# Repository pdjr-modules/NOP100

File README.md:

# NOP100

The **NOP100** project implements an
[NMEA 2000](https://en.wikipedia.org/wiki/NMEA_2000)
interface module with twin
[MikroBUS](https://www.mikroe.com/mikrobus)
sockets which allow specialisation of function by the addition of
[Click](https://www.mikroe.com/click) expansion cards.

[**NOP100** hardware](./hardware/README.md)
is based on the Teensy 4.0 micro-controller supported by a CAN
transceiver, parasitic power supply and a user configuration
interface.

[**NOP100** firmware](./firmware/README.md)
manages NMEA 2000 connectivity, user interaction and module
configuration and is easily extended by the addition of firmware
dedicated to operation of the installed MikroBus cards and the
integration of their function with NMEA 2000.

## Project organisation

```
NOP100/
  + firmware/            # NOP100 firmware...
    + modules/           # Folders for module specialisations
      + NOP100-SIM/        # Specialisation defining an NMEA switch input module
        + defines.h
        + definitions.h
        + includes.h
        + loop.h
        + setup.h
      + another module specialisation/
      + .../
    + NOP100.cpp         # NOP100 main application 
    + README.md
    + defines.h          # Symbolic link to a module specialisation
    + definitions.h      #   "       "
    + includes.h         #   "       "
    + loop.h             #   "       "
    + setup.h            #   "       "
  + hardware/            # NOP100 hardware...
    + gerber/            # Gerber files for PCB fabrication
    + kicad/             # Kicad design for the NOP100 motherboard
    + README.md
```

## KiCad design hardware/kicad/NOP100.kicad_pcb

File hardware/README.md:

# NOP100 hardware

This project thread provides a circuit design and PCB layout for an
NMEA 2000 interface module which uses
[MikroBus](https://www.mikroe.com/mikrobus)
[Click](https://mikroe.com/click) cards as its real-world interfaces.

The module is based on the
[Teensy 4.0](https://www.pjrc.com/teensy_40)
micro-controller supported by an
[MCP2551](https://www.microchip.com/en-us/product/mcp2551)
CAN transceiver, and single or twin
[Murata](https://www.murata.com/en-eu/)
power supplies.

<table border="0">
<tr>
<td width="50%">

</td>
<td>

</td>
</tr>
</table>

See [NOP100/firmware](../firmware/) for a C++ pattern and associated
libraries that can be used as a basis for implementing firmware which
exploits this hardware design.

## Design elements

### PCB and enclosure

The four-layer PCB is suitable for use in a
[Hammond 1591GSFLBK case](https://docs.rs-online.com/b790/A700000007521666.pdf)
and uses both surface-mount and through-hole components.

### Microcontroller

[Teensy 4.0](https://www.pjrc.com/store/teensy40.html).

### Power supplies

The module is a dual-voltage (5VDC/3.3VDC) design and is powered from
the host NMEA bus 12VDC supply.

A DC-DC converter outputs 5VDC 400mA to the microcontroller and CAN
transceiver.
In situations where the installed MikroBus modules have a current draw
of less that 250mA the Teensy's on-board 3.3VDC voltage regulator can
be used as the supply for all 3.3VDC consumers by making a solder
bridge connection at JP1.

If the Teensy's 250mA limit is insufficient for MikroBus consumers,
then a 3.3VDC 600mA DC-DC converter can be installed on the module PCB
(in which case the solder-bridge connection must not be made).

### CAN interface

An MCP-2551/IP CAN transceiver converts data on the NMEA bus
(CAN-H/CAN-L) to signals suitable for use by the microcontroller CAN
interface.
Input and output signals are level-shifted to 3.3VDC for compatability
with the Teensy 4.0.

A switch switch-selectable 120 Ohm bus termination resistor allows the
module to be used as either an NMEA drop or terminal node and a second
switch allows the NMEA bus shield to be connected to the module GND.

An activity indicator LED shows when the CAN interface is transmitting.

### Configuration interface

The configuration interface consists of two 4-bit rotary switches, a
momentary tactile switch and an LED.
The rotary switches are used to set the module's NMEA instance but can
also be used in concert with the tactile switch to save module
configuration parameters to EEPROM.

### MikroBus sockets

The **NOP100** hardware is specialised by inserting appropriate MikroBus
Click modules into the two MikroBus connector sockets.

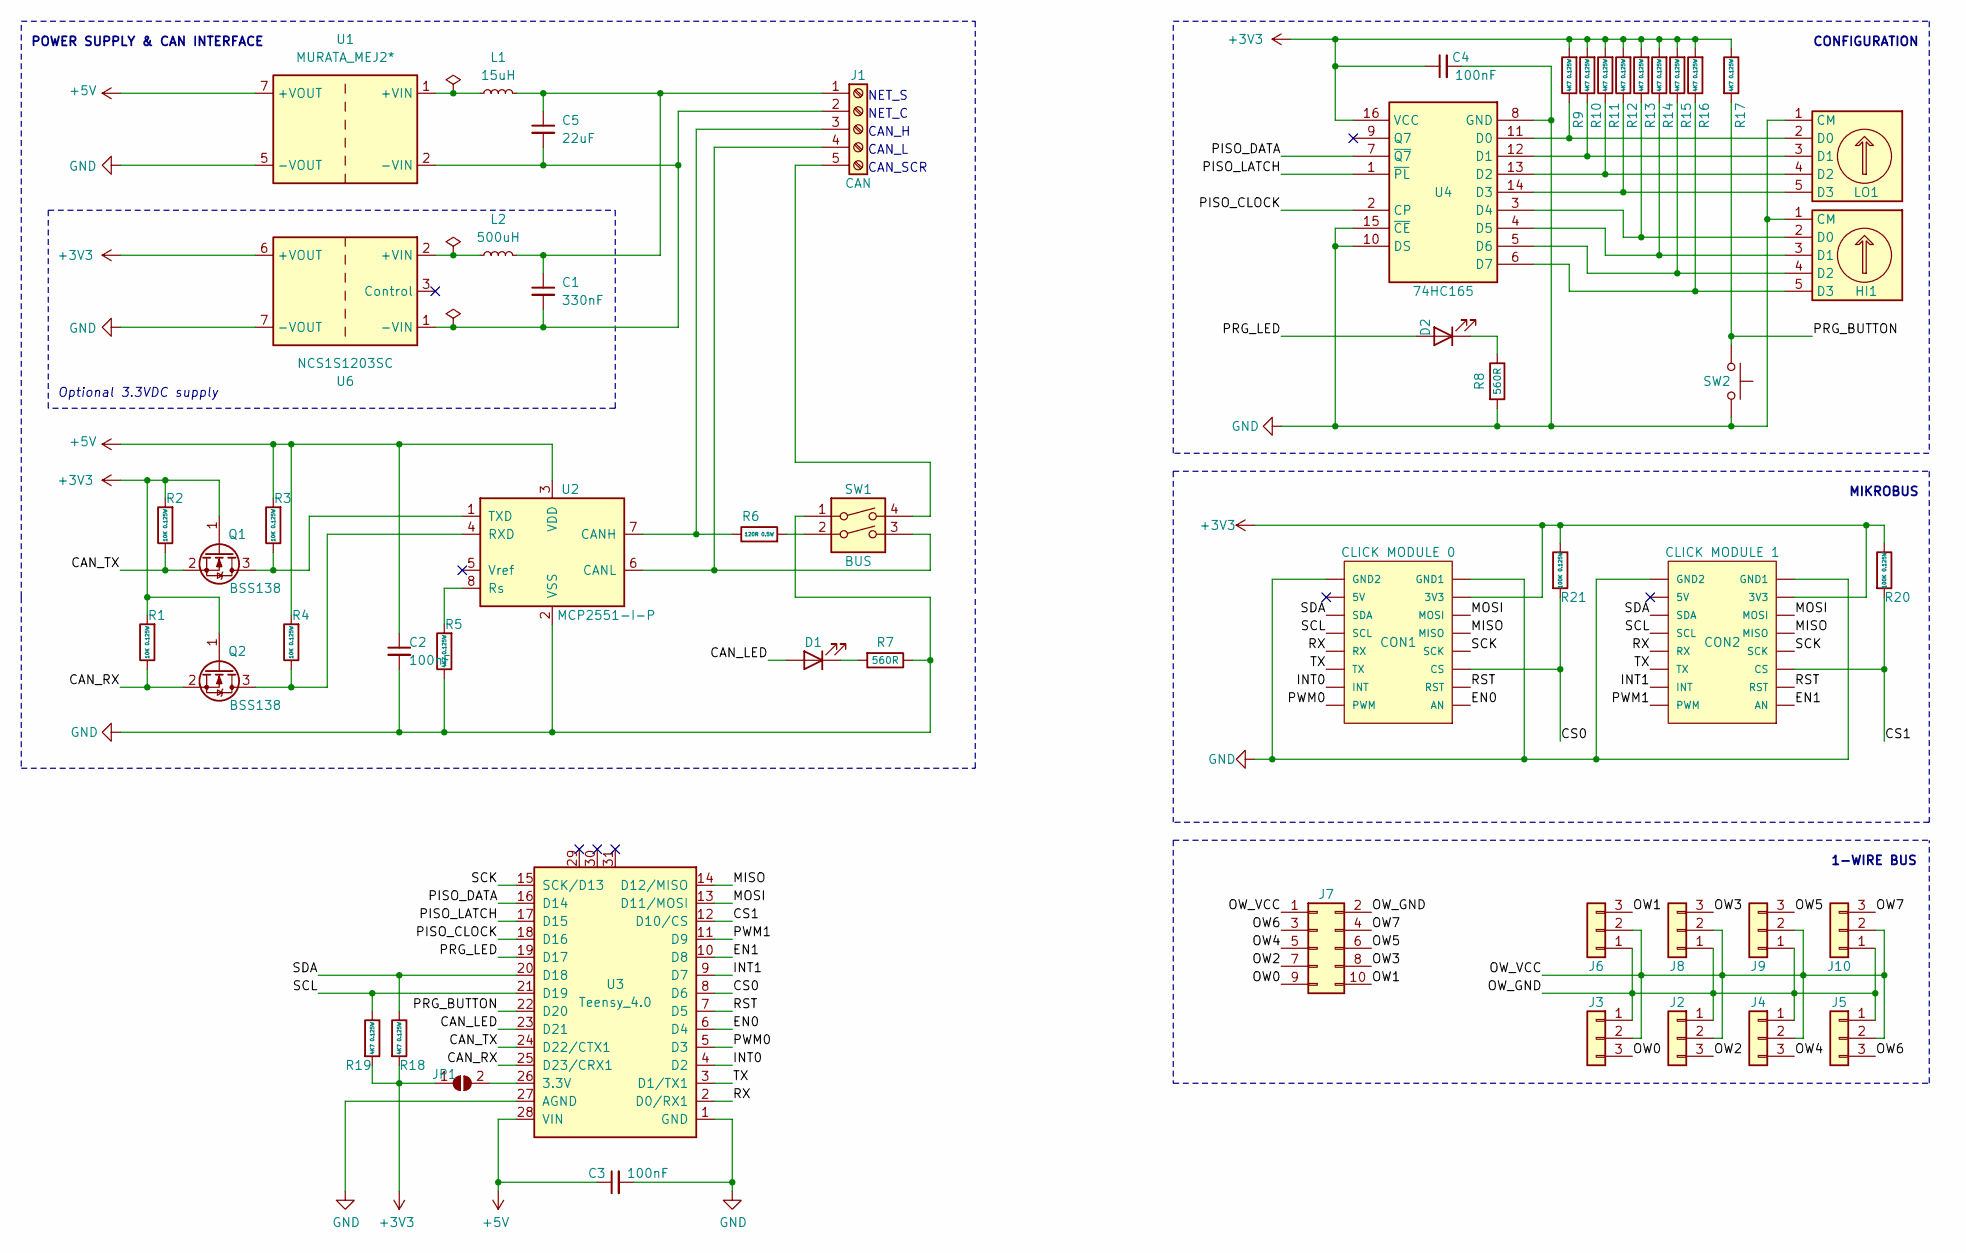
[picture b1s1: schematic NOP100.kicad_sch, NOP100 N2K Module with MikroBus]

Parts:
C1: 330nF; R_1210_3225Metric
C2, C3, C4: 100nF; R_0805_2012Metric
C5: 22uF; R_1210_3225Metric
CON1: CLICK MODULE 0; MIKROBUS_HOST_CONN
CON2: CLICK MODULE 1; MIKROBUS_HOST_CONN
D1: LED; LED_Kingbright_APHBM2012_2x1.25mm
D2: LED; R_0805_2012Metric
HI1: SW_Coded; Nidec_Copal_SH-7010C
J1: CAN; PinHeader_1x05_P2.54mm_Vertical
J2, J3, J4, J5, J6, J8, J9, J10: Conn_01x03; RS_8971054
J7: Conn_02x05_Odd_Even; PinSocket_2x05_P2.54mm_Vertical
JP1: SolderJumper_2_Open; SolderJumper-2_P1.3mm_Bridged_RoundedPad1.0x1.5mm
L1: 15uH; L_Bourns_SRN6045TA
L2: 500uH; L_Bourns_SRN6045TA
LO1: SW_Coded; Nidec_Copal_SH-7010C
Q1, Q2: BSS138; SOT-23
R1, R2, R3, R4: 10K 0.125W; R_0805_2012Metric
R5, R9, R10, R11, R12, R13, R14, R15, R16, R17, R18, R19: 4K7 0.125W; R_0805_2012Metric
R6: 120R 0.5W; R_1206_3216Metric
R7, R8: 560R; R_0805_2012Metric
R20, R21: 100K 0.125W; R_0805_2012Metric
SW1: BUS; DIP-4_W7.62mm_LongPads
SW2: SW_Push; SW_SPST_PTS810
U1: MURATA_MEJ2*; Murata-MEJ2*
U2: MCP2551-I-P; SOIC-8_3.9x4.9mm_P1.27mm
U3: Teensy_4.0; DIP-28_W15.24mm
U4: 74HC165; SOIC-16_3.9x9.9mm_P1.27mm
U6: NCS1S1203SC; Converter_DCDC_Murata_NCS1SxxxxSC_THT

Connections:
+3V3: C4.1, CON1.P7 (3V3), CON2.P7 (3V3), JP1.1 (A), Q1.1 (G), Q2.1 (G), R1.2, R2.2, R9.2, R10.2, R11.2, R12.2, R13.2, R14.2, R15.2, R16.2, R17.1, R18.2, R19.2, R20.1, R21.1, U4.16 (VCC), U6.6 (+VOUT)
+5V: C2.1, C3.1, R3.2, R4.2, U1.7 (+VOUT), U2.3 (VDD), U3.28 (VIN)
/CAN_LED: D1.2 (A), U3.23 (D21)
/CAN_RX: Q2.2 (S), R1.1, U3.25 (D23/CRX1)
/CAN_TX: Q1.2 (S), R2.1, U3.24 (D22/CTX1)
/CS0: CON1.P3 (CS), R21.2, U3.8 (D6)
/CS1: CON2.P3 (CS), R20.2, U3.12 (D10/CS)
/EN0: CON1.P1 (AN), U3.6 (D4)
/EN1: CON2.P1 (AN), U3.10 (D8)
/INT0: CON1.P15 (INT), U3.4 (D2)
/INT1: CON2.P15 (INT), U3.9 (D7)
/MISO: CON1.P5 (MISO), CON2.P5 (MISO), U3.14 (D12/MISO)
/MOSI: CON1.P6 (MOSI), CON2.P6 (MOSI), U3.13 (D11/MOSI)
/OW0: J3.3, J7.9
/OW1: J6.3, J7.10
/OW2: J2.3, J7.7
/OW3: J7.8, J8.3
/OW4: J4.3, J7.5
/OW5: J7.6, J9.3
/OW6: J5.3, J7.3
/OW7: J7.4, J10.3
/OW_GND: J2.1, J3.1, J4.1, J5.1, J6.1, J7.2, J8.1, J9.1, J10.1
/OW_VCC: J2.2, J3.2, J4.2, J5.2, J6.2, J7.1, J8.2, J9.2, J10.2
/PISO_CLOCK: U3.18 (D16), U4.2 (CP)
/PISO_DATA: U3.16 (D14), U4.7 (~Q7)
/PISO_LATCH: U3.17 (D15), U4.1 (~PL)
/PRG_BUTTON: R17.2, SW2.1, U3.22 (D20)
/PRG_LED: D2.2 (A), U3.19 (D17)
/PWM0: CON1.P16 (PWM), U3.5 (D3)
/PWM1: CON2.P16 (PWM), U3.11 (D9)
/RST: CON1.P2 (RST), CON2.P2 (RST), U3.7 (D5)
/RX: CON1.P13 (RX), CON2.P13 (RX), U3.2 (D0/RX1)
/SCK: CON1.P4 (SCK), CON2.P4 (SCK), U3.15 (SCK/D13)
/SCL: CON1.P12 (SCL), CON2.P12 (SCL), R19.1, U3.21 (D19)
/SDA: CON1.P11 (SDA), CON2.P11 (SDA), R18.1, U3.20 (D18)
/TX: CON1.P14 (TX), CON2.P14 (TX), U3.3 (D1/TX1)
GND: C2.2, C3.2, C4.2, CON1.P8 (GND1), CON1.P9 (GND2), CON2.P8 (GND1), CON2.P9 (GND2), HI1.1 (CM), LO1.1 (CM), R5.1, R7.1, R8.2, SW1.1, SW2.2, U1.5 (-VOUT), U2.2 (VSS), U3.1 (GND), U3.27 (AGND), U4.8 (GND), U4.10 (DS), U4.15 (~CE), U6.7 (-VOUT)
unnamed: D1.1 (K), R7.2
unnamed: D2.1 (K), R8.1
unnamed: HI1.2 (D0), R13.1, U4.3 (D4)
unnamed: HI1.3 (D1), R14.1, U4.4 (D5)
unnamed: HI1.4 (D2), R15.1, U4.5 (D6)
unnamed: HI1.5 (D3), R16.1, U4.6 (D7)
unnamed: C1.1, C5.1, J1.1, L1.2, L2.2
unnamed: C1.2, C5.2, J1.2, U1.2 (-VIN), U6.1 (-VIN)
unnamed: J1.3, R6.1, U2.7 (CANH)
unnamed: J1.4, SW1.3, U2.6 (CANL)
unnamed: J1.5, SW1.4
unnamed: JP1.2 (B), U3.26 (3.3V)
unnamed: LO1.2 (D0), R9.1, U4.11 (D0)
unnamed: LO1.3 (D1), R10.1, U4.12 (D1)
unnamed: LO1.4 (D2), R11.1, U4.13 (D2)
unnamed: LO1.5 (D3), R12.1, U4.14 (D3)
unnamed: Q1.3 (D), R3.1, U2.1 (TXD)
unnamed: Q2.3 (D), R4.1, U2.4 (RXD)
unnamed: R6.2, SW1.2
unnamed: L1.1, U1.1 (+VIN)
unnamed: R5.2, U2.8 (Rs)
unnamed: L2.1, U6.2 (+VIN)

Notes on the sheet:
CONFIGURATION
1-WIRE BUS
MIKROBUS
CAN_H
POWER SUPPLY & CAN INTERFACE
CAN_L
CAN_SCR
NET_C
NET_S
Optional 3.3VDC supply

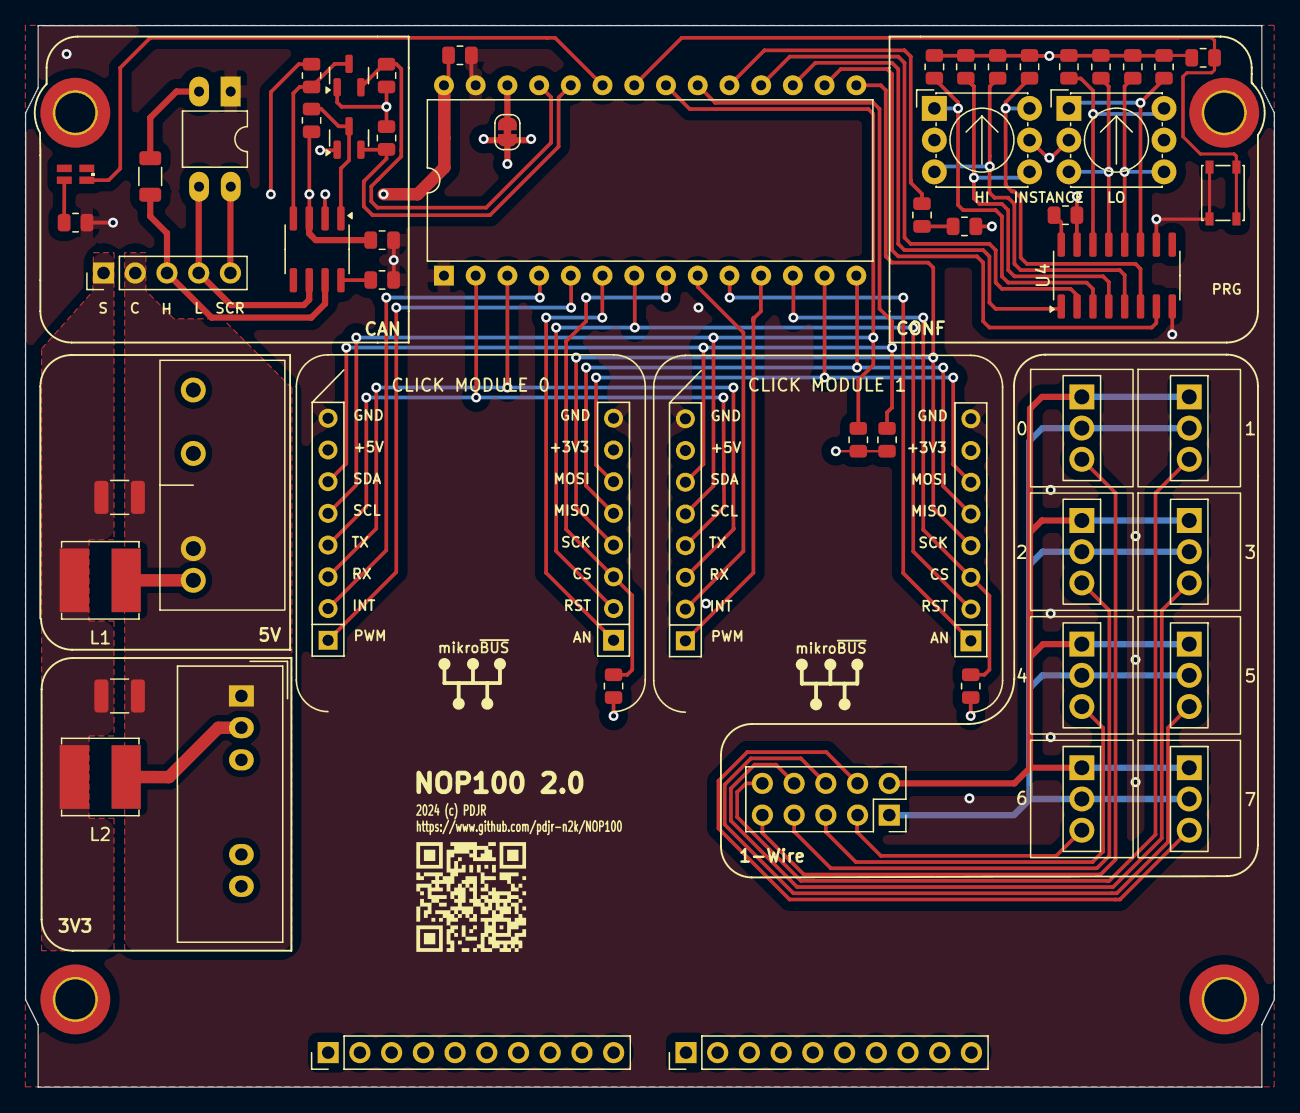
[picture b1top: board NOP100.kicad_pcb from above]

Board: 4 copper layers, 100.0 x 85.0 mm, 54 parts (0 on the bottom side), 59 nets.

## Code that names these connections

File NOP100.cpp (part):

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#define GPIO_SIPO_DATA 0
#define GPIO_SIPO_LATCH 1
#define GPIO_SIPO_CLOCK 2
#define GPIO_CAN_TX 3
#define GPIO_CAN_RX 4
#define GPIO_D5 5
#define GPIO_D6 6
#define GPIO_D7 7
#define GPIO_D8 8
#define GPIO_D9 9
#define GPIO_PISO_DATA 10
#define GPIO_PISO_LATCH 11
#define GPIO_PISO_CLOCK 12
#define GPIO_POWER_LED 13
#define GPIO_PRG 14
#define GPIO_TRANSMIT_LED 15
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#define GPIO_D21 21
#define GPIO_D22 22
#define GPIO_D23 23
#define GPIO_OUTPUT_PINS { GPIO_SIPO_CLOCK, GPIO_SIPO_DATA, GPIO_SIPO_LATCH, GPIO_PISO_CLOCK, GPIO_PISO_LATCH, GPIO_POWER_LED, GPIO_TRANSMIT_LED }

#define NMEA2000_SOURCE_ADDRESS_SEED 22     // Arbitrary seed value
#define NMEA2000_INSTANCE_UNDEFINED 255     // NMEA defines 255 as "undefined"
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tNMEA2000Handler NMEA2000Handlers[] = NMEA_PGN_HANDLERS;

/**********************************************************************
 * PRG_BUTTON - debounced GPIO_PRG.
 */
Button PRG_BUTTON(GPIO_PRG);
StateMachine::tJump jumpVectors[] PRG_JUMP_VECTOR;
StateMachine STATE_MACHINE(0, jumpVectors);

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 * DIL_SWITCH - interface to the IC74HC165 IC that connects the eight
 * DIL switch parallel inputs.
 */
IC74HC165 DIL_SWITCH (GPIO_PISO_CLOCK, GPIO_PISO_DATA, GPIO_PISO_LATCH);

/**********************************************************************
 * MODULE_INSTANCE - working storage for the module instance number.
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
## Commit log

2022-12-15 First upload
2022-12-15 Refactor
2022-12-17 Refactor.
2022-12-17 Tidy up
2022-12-18 Create SIM108.code-workspace
2022-12-21 Add code
2022-12-21 Documentation updates.
2022-12-21 Add configureModuleInstance
2022-12-21 Add testpomts
2022-12-22 Move grid
2022-12-22 Documentation
2022-12-22 Silkscreen
2022-12-22 Silk edit.
2022-12-22 Notes.
2022-12-22 Readme
2022-12-22 Add settings
2022-12-23 Tweak
2022-12-24 Create firmware
2022-12-27 Create NOP100.code-workspace
2022-12-27 Tweaks
2023-01-04 Revise operation of transmit LED
2023-01-07 Update NOP100.cpp
    Use lamda expressions rather than callback functions.
2023-01-10 Revise change handler
2023-01-11 Revise interaction
2023-01-11 Stuff
2023-01-16 Doxygen documentation
2023-01-17 Remove doc
2023-01-20 Refactor configuration handling
2023-01-20 Refactor interaction
2023-01-21 Refactor of interacation complete
2023-01-21 Tweak.
2023-01-24 Clean up
2024-07-13 Convert micro vias to through vias.
2024-07-13 Revise mikrobus symbol
2024-07-13 Update README.
2024-07-14 Add 3.3VDC alternatives.
2024-07-15 Library tweak
2024-07-15 Gerbers
2024-07-15 Create Gerbers
2024-07-16 Tidy up redundant configuration entries.
2024-07-20 Lots of tweaks
2024-07-21 Tweaks.
2024-07-22 Update GPIO assignments.
2024-07-22 Rebuild.
2024-07-23 Switch build.
2024-07-25 Accommodate library change.
2024-07-27 New build
2024-07-27 Add 1-wire support
2024-07-30 Adjust fill zones.

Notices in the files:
NOP100.cpp:
Copyright (c) 2021-22 Paul Reeve <preeve@pdjr.eu>
